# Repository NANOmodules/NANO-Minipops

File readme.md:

# NANO - Minipops

Arduino project based in Minipops design by Jan Ostman (DSP Synthesizers) 

The hardware consists in an Arduino Uno including it shield with 9 slide switches, 2 rotary potentiometers and 1 LED. 
Software in the CODE folder contains all the necessary to convert your Arduino Uno in a Minipops drum box.

**Click on the image to watch the presentation video!**

Link of the video: https://www.youtube.com/watch?v=v7ahzl_3tDo&t=2s
	
Jan project info: https://janostman.wordpress.com/the-o2-source-code/

This Github contains the information needed to build and flash an Arduino Minipops shield.

## Contents

Contents are divided in the following categories:

### BOM

```
Include the component list, with it’s values and additional information.
```

### CODE

```
Arduino sketch with the code needed to run the device.
```

### DESIGN FILES

```
KiCad files for the project, including schematic, PCB and the project itself.
```

### GERBERS

```
PCB fabrication files.
```

### SCHEMATIC

```
Electronic circuit design.
```

## Authors

* **Jorge Gutiérrez** - *NANO Modules* 

## License

This project is licensed under **CC BY-NC-SA 4.0** 

## About

**NANO Modules**

Instagram: @NANOmodules							

Facebook:  /NANOmodules

València - SPAIN 2018

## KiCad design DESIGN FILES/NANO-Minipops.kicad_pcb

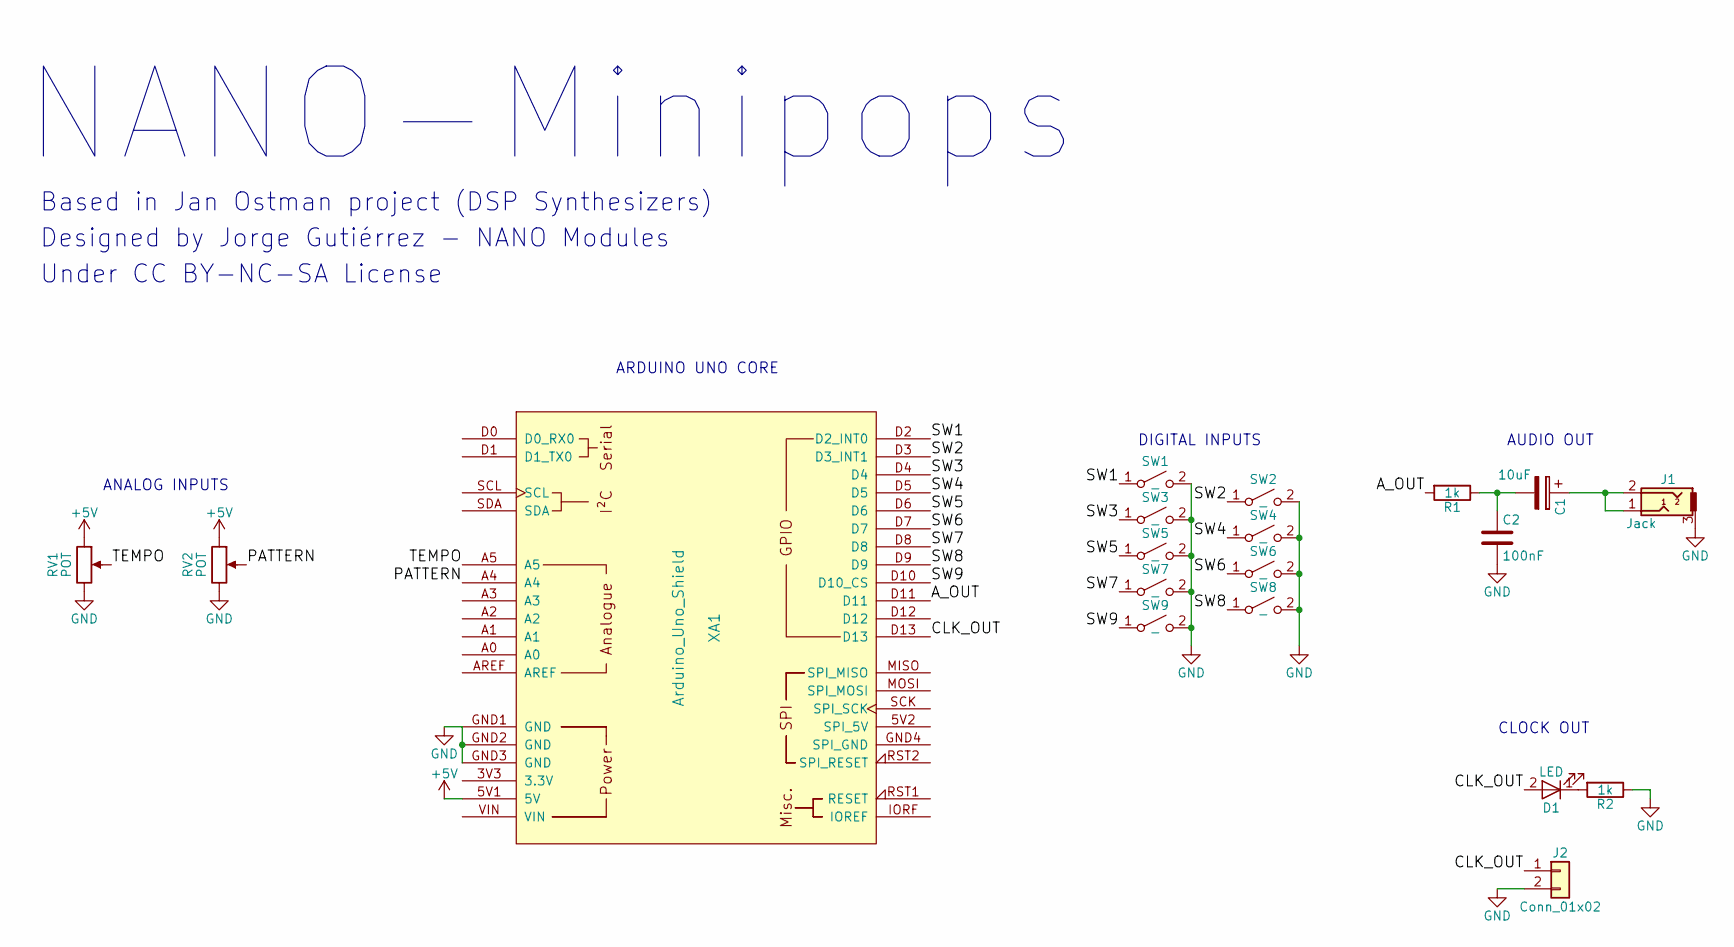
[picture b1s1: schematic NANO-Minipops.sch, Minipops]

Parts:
C1: 10uF; CP_Radial_D6.3mm_P2.50mm
C2: 100nF; C_Rect_L7.0mm_W2.0mm_P5.00mm
D1: LED; LED_D3.0mm
J1: Jack; Jack-CUI
J2: Conn_01x02; Pin_Header_Straight_1x02_Pitch2.54mm
R1, R2: 1k; Resistor_SMD+THTuniversal_0805to1206_RM10_HandSoldering
RV1, RV2: POT; Potentiometer_Alps_RK09K_Horizontal
SW1, SW2, SW3, SW4, SW5, SW6, SW7, SW8, SW9: _; SlideSwitch
XA1: Arduino_Uno_Shield

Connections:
+5V: RV1.1, RV2.1, XA1.5V1 (5V)
/A_OUT: R1.2, XA1.D11
/CLK_OUT: D1.2 (A), J2.1, XA1.D13
/PATTERN: RV2.2, XA1.A4
/SW1: SW1.1 (A), XA1.D2 (D2_INT0)
/SW2: SW2.1 (A), XA1.D3 (D3_INT1)
/SW3: SW3.1 (A), XA1.D4
/SW4: SW4.1 (A), XA1.D5
/SW5: SW5.1 (A), XA1.D6
/SW6: SW6.1 (A), XA1.D7
/SW7: SW7.1 (A), XA1.D8
/SW8: SW8.1 (A), XA1.D9
/SW9: SW9.1 (A), XA1.D10 (D10_CS); also elsewhere on the board
/TEMPO: RV1.2, XA1.A5
GND: C2.2, J1.3, J2.2, R2.1, RV1.3, RV2.3, SW1.2 (B), SW2.2 (B), SW3.2 (B), SW4.2 (B), SW5.2 (B), SW6.2 (B), SW7.2 (B), SW8.2 (B), SW9.2 (B), XA1.GND1 (GND), XA1.GND2 (GND), XA1.GND3 (GND); also elsewhere on the board
unnamed: C1.1, J1.1, J1.2
unnamed: C1.2, C2.1, R1.1
unnamed: D1.1 (K), R2.2

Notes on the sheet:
CLOCK OUT
AUDIO OUT
ARDUINO UNO CORE
ANALOG INPUTS
DIGITAL INPUTS
NANO-Minipops
Based in Jan Ostman project (DSP Synthesizers)
Designed by Jorge Gutiérrez - NANO Modules
Under CC BY-NC-SA License

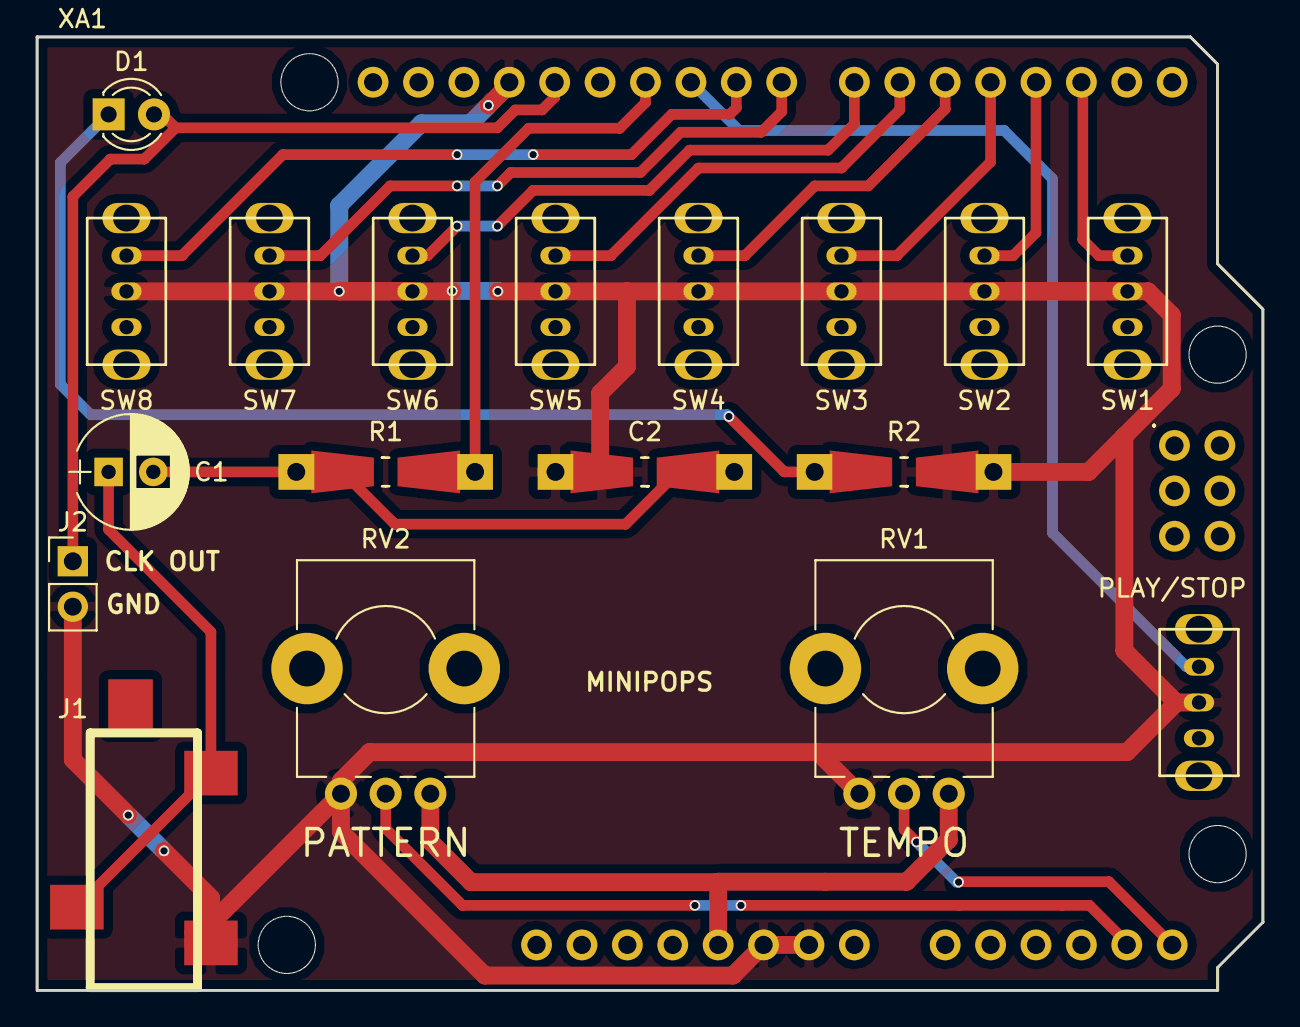
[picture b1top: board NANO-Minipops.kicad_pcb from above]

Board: 2 copper layers, 68.6 x 53.3 mm, 19 parts (0 on the bottom side), 18 nets.

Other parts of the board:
PLAY/STOP: _; SlideSwitch

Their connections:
/SW9: PLAY/STOP.1; also elsewhere on the board
GND: PLAY/STOP.2; also elsewhere on the board

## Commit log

2018-03-25 Adding things
2018-03-25 Improved PCB
2018-03-25 Added BOM
2018-03-25 Testing Readme
2018-03-25 Improved Readme
2018-03-25 Added info
2018-03-25 Expanded readme
2018-03-25 Readme
2018-03-25 Set theme jekyll-theme-cayman
2018-03-25 Added Video
2018-03-25 Included Video
2018-03-25 Changed image
2018-03-25 Fixed Image
2018-03-25 Added Text
2018-03-27 Fixed Code
2018-05-03 Improved CLK
2018-05-03 Improved CLK accuracy
2018-05-20 Improved CLK out
2018-09-25 Added TEST
2018-10-17 Image
2018-10-24 Updated - Workshop
2018-10-30 Put declarations on Includes.h to make it compatible with Arduino 1.6.5

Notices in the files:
DESIGN FILES/NANO-Minipops.kicad_pcb:
UNDER CC BY-NC-SA 4.0 LICENSE
